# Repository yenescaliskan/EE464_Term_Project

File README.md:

# EE464_Term_Project
In this project, an isolated DC-DC converter (Push-Pull Converter) will be designed and implemented. Required converter will have 12-18V input voltage range and 48V output voltage. Output voltage will have at most 3% voltage ripple and output power rating will be 48W. Deviation of percent output voltage when input voltage is changed from its minimum to maximum will be at most 3%. Deviation of percent output voltage when load current is changed from 10% to 100% will be at most 3%.

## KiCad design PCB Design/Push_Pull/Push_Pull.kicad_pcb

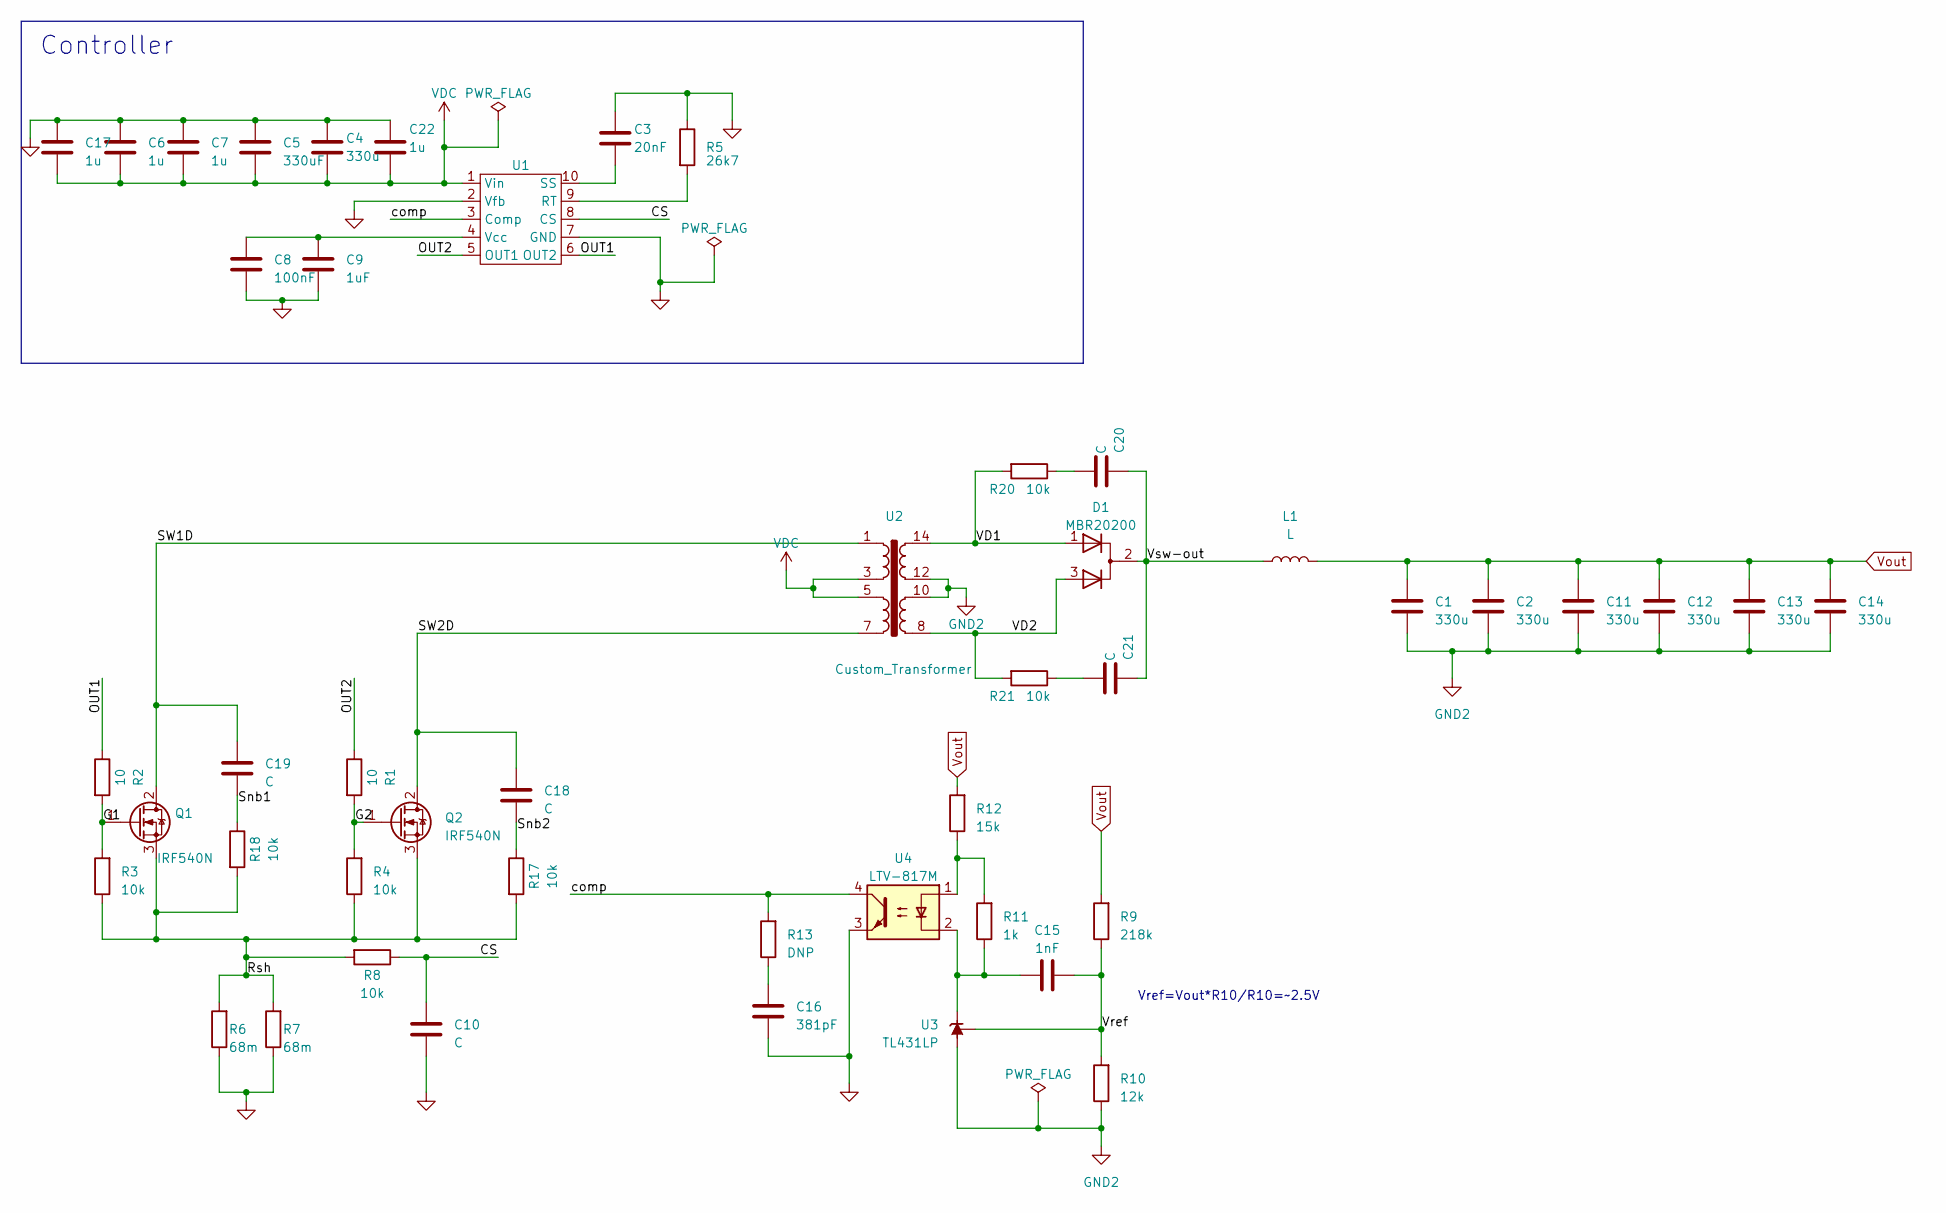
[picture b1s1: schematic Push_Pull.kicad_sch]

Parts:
C1, C2, C4, C11, C12, C13, C14: 330u; CP_Radial_D8.0mm_P5.00mm
C3: 20nF; C_Disc_D5.0mm_W2.5mm_P5.00mm
C5: 330uF; CP_Radial_D8.0mm_P5.00mm
C6, C7, C17, C22: 1u; C_0805_2012Metric
C8: 100nF; C_0603_1608Metric
C9: 1uF; C_0603_1608Metric
C10: C; C_Disc_D5.0mm_W2.5mm_P5.00mm
C15: 1nF; C_Disc_D5.1mm_W3.2mm_P5.00mm
C16: 381pF; C_Disc_D5.0mm_W2.5mm_P5.00mm
C18, C19: C; C_1206_3216Metric
C20, C21: C; C_Disc_D7.5mm_W5.0mm_P7.50mm
D1: MBR20200; TO-220-3_Vertical
L1: L; L_Toroid_Vertical_L25.4mm_W14.7mm_P12.20mm_Vishay_TJ5
Q1, Q2: IRF540N; TO-220-3_Vertical
R1, R2: 10; R_4020_10251Metric
R3, R4, R8: 10k; R_4020_10251Metric
R5: 26k7; R_Axial_DIN0204_L3.6mm_D1.6mm_P7.62mm_Horizontal
R6, R7: 68m; R_2512_6332Metric_Pad1.40x3.35mm_HandSolder
R9: 218k; R_Axial_DIN0207_L6.3mm_D2.5mm_P10.16mm_Horizontal
R10: 12k; R_Axial_DIN0207_L6.3mm_D2.5mm_P10.16mm_Horizontal
R11: 1k; R_Axial_DIN0207_L6.3mm_D2.5mm_P10.16mm_Horizontal
R12: 15k; R_Axial_DIN0207_L6.3mm_D2.5mm_P10.16mm_Horizontal
R13: DNP; R_Axial_DIN0204_L3.6mm_D1.6mm_P5.08mm_Horizontal
R17, R18: 10k; R_1206_3216Metric
R20, R21: 10k; R_Axial_DIN0207_L6.3mm_D2.5mm_P10.16mm_Horizontal
U1: DIP-10_W7.62mm
U2: Custom_Transformer; ETD34-14pin
U3: TL431LP; TO-92_Inline
U4: LTV-817M; DIP-4_W10.16mm

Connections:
/CS: C10.1, R8.1, U1.8 (CS)
/G1: Q1.1 (G), R2.2, R3.2
/G2: Q2.1 (G), R1.2, R4.2
/OUT1: R2.1, U1.6 (OUT2)
/OUT2: R1.1, U1.5 (OUT1)
/Rsh: Q1.3 (S), Q2.3 (S), R3.1, R4.1, R6.2, R7.2, R8.2, R17.2, R18.2
/SW1D: C19.1, Q1.2 (D), U2.1
/SW2D: C18.1, Q2.2 (D), U2.7
/Snb1: C19.2, R18.1
/Snb2: C18.2, R17.1
/VD1: D1.1 (K), R20.2, U2.14
/VD2: D1.3 (K), R21.2, U2.8
/Vref: C15.2, R9.1, R10.2, U3.1 (REF)
/Vsw-out: C20.1, C21.1, D1.2 (A), L1.1
/comp: R13.2, U1.3 (Comp), U4.4
GND: C3.1, C4.2, C5.2, C6.1, C7.1, C8.2, C9.2, C10.2, C16.1, C17.1, C22.1, R5.1, R6.1, R7.1, U1.2 (Vfb), U1.7 (GND), U4.3
GND2: C1.2, C2.2, C11.2, C12.2, C13.2, C14.2, R10.1, U2.10, U2.12, U3.2 (A)
unnamed: C16.2, R13.1
unnamed: C20.2, R20.1
unnamed: C21.2, R21.1
unnamed: R11.2, R12.1, U4.1
unnamed: R5.2, U1.9 (RT)
unnamed: C3.2, U1.10 (SS)
unnamed: C8.1, C9.1, U1.4 (Vcc)
unnamed: C15.1, R11.1, U3.3 (K), U4.2
VDC: C4.1, C5.1, C6.2, C7.2, C17.2, C22.2, U1.1 (Vin), U2.3, U2.5
Vout: C1.1, C2.1, C11.1, C12.1, C13.1, C14.1, L1.2, R9.2, R12.2

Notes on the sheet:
Controller
Vref=Vout*R10/R10=~2.5V

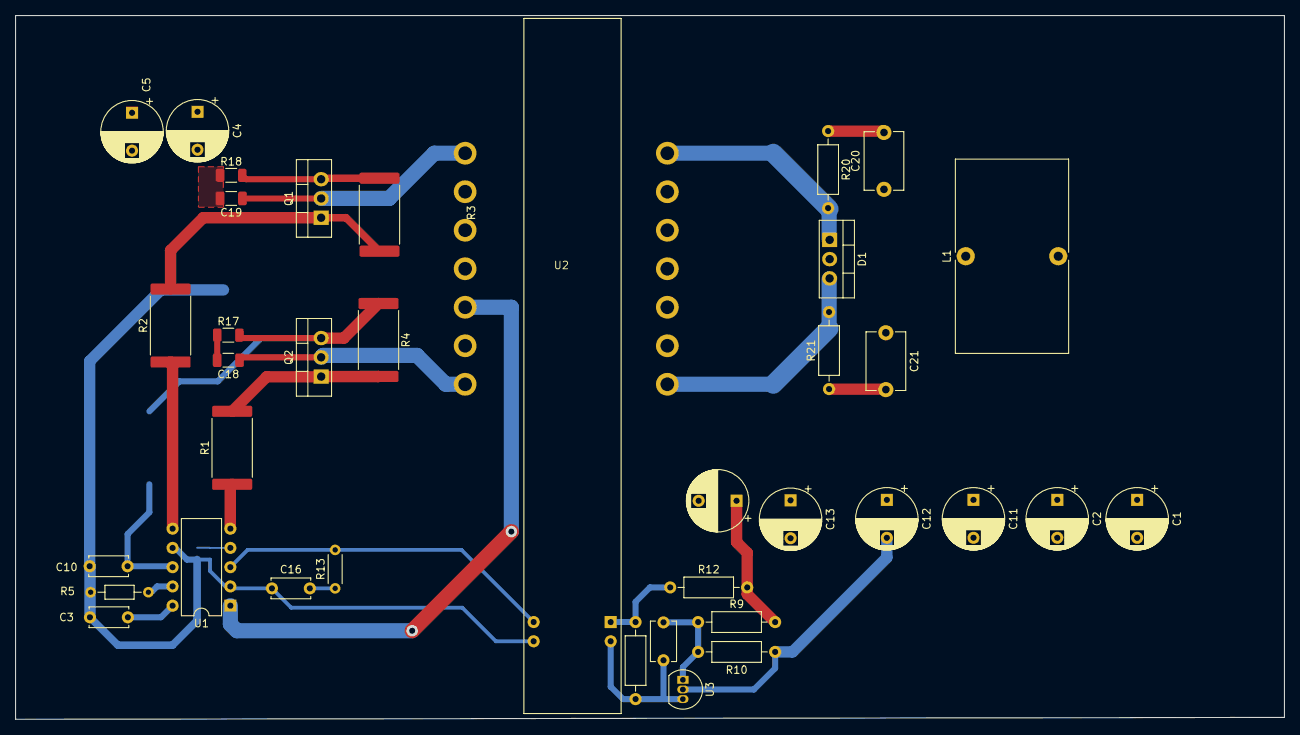
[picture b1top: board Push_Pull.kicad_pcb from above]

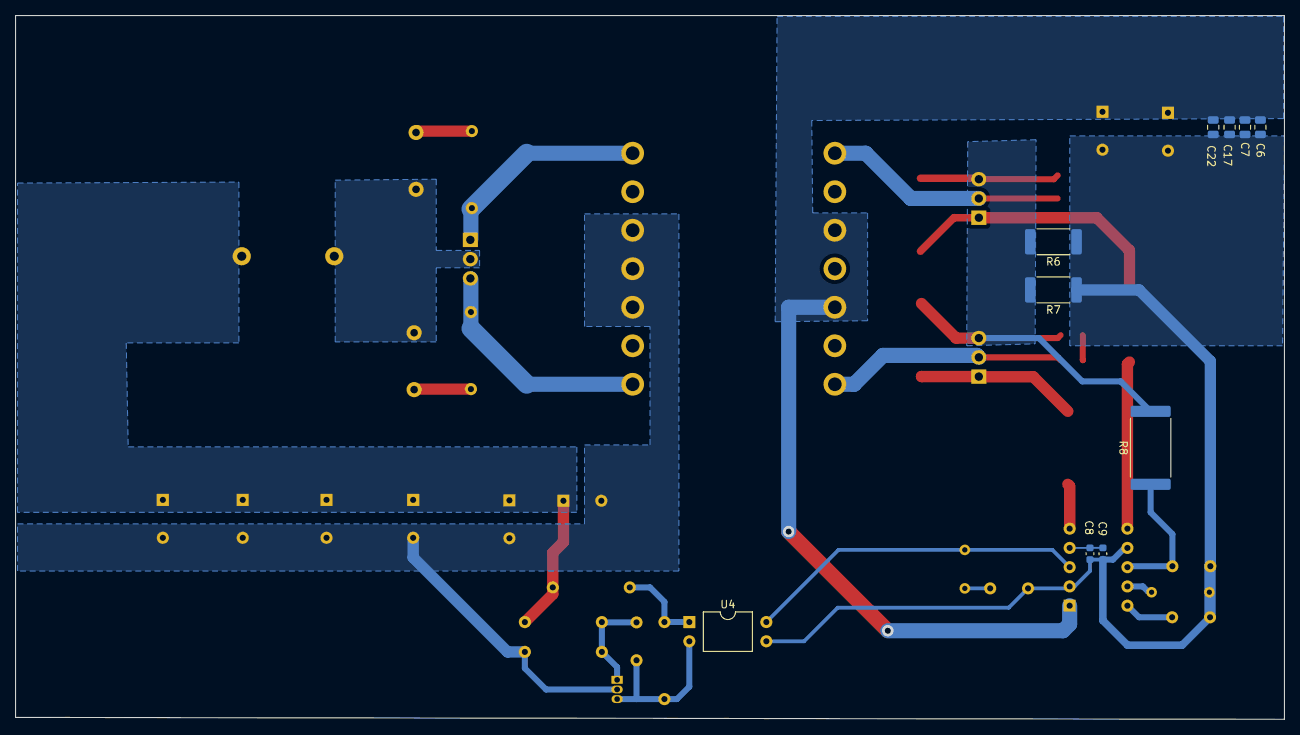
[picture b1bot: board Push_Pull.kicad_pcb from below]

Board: 2 copper layers, 167.4 x 92.8 mm, 47 parts (10 on the bottom side), 27 nets.

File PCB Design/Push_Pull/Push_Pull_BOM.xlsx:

Source: | C:\Users\smlmc\Documents\EE464_Term_Project\PCB Design\Push_Pull\Push_Pull.kica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
Date: | 45105.013958333337
Tool: | Eeschema 7.0.2
Generator: | C:\Program Files\KiCad\7.0\bin\scripting\plugins/bom_csv_grouped_by_value.py
Component Count: | 47
Collated Components:
Item | Qty | Reference(s) | Value | LibPart | Footprint | Datasheet | DNP
1 | 7 | C1, C2, C4, C11, C12, C13, C14 | 330u | Device:C | Capacitor_THT:CP_Radial_D8.0mm_P5.00mm | ~
2 | 1 | C3 | 20nF | Device:C | Capacitor_THT:C_Disc_D5.0mm_W2.5mm_P5.00mm | ~
3 | 1 | C5 | 330uF | Device:C | Capacitor_THT:CP_Radial_D8.0mm_P5.00mm | ~
4 | 4 | C6, C7, C17, C22 | 1u | Device:C | Capacitor_SMD:C_0805_2012Metric | ~
5 | 1 | C8 | 100nF | Device:C | Capacitor_SMD:C_0603_1608Metric | ~
6 | 1 | C9 | 1uF | Device:C | Capacitor_SMD:C_0603_1608Metric | ~
7 | 1 | C10 | C | Device:C | Capacitor_THT:C_Disc_D5.0mm_W2.5mm_P5.00mm | ~
8 | 1 | C15 | 1nF | Device:C | Capacitor_THT:C_Disc_D5.1mm_W3.2mm_P5.00mm | ~
9 | 1 | C16 | 381pF | Device:C | Capacitor_THT:C_Disc_D5.0mm_W2.5mm_P5.00mm | ~
10 | 2 | C18, C19 | C | Device:C | Capacitor_SMD:C_1206_3216Metric | ~
11 | 2 | C20, C21 | C | Device:C | Capacitor_THT:C_Disc_D7.5mm_W5.0mm_P7.50mm | ~
12 | 1 | D1 | MBR20200 | Device:D_Dual_CommonCathode_AKA_Parallel | Package_TO_SOT_THT:TO-220-3_Vertical | ~
13 | 1 | L1 | L | Device:L | Inductor_THT:L_Toroid_Vertical_L25.4mm_W14.7mm_P12.20mm_Vishay_TJ5 | ~
14 | 2 | Q1, Q2 | IRF540N | Transistor_FET:IRF540N | Package_TO_SOT_THT:TO-220-3_Vertical | http://www.irf.com/product-info/datasheets/data/irf540n.pdf
15 | 2 | R1, R2 | 10 | Device:R | Resistor_SMD:R_4020_10251Metric | ~
16 | 3 | R3, R4, R8 | 10k | Device:R | Resistor_SMD:R_4020_10251Metric | ~
17 | 1 | R5 | 26k7 | Device:R | Resistor_THT:R_Axial_DIN0204_L3.6mm_D1.6mm_P7.62mm_Horizontal | ~
18 | 2 | R6, R7 | 68m | Device:R | Resistor_SMD:R_2512_6332Metric_Pad1.40x3.35mm_HandSolder | ~
19 | 1 | R9 | 218k | Device:R | Resistor_THT:R_Axial_DIN0207_L6.3mm_D2.5mm_P10.16mm_Horizontal | ~
20 | 1 | R10 | 12k | Device:R | Resistor_THT:R_Axial_DIN0207_L6.3mm_D2.5mm_P10.16mm_Horizontal | ~
21 | 1 | R11 | 1k | Device:R | Resistor_THT:R_Axial_DIN0207_L6.3mm_D2.5mm_P10.16mm_Horizontal | ~
22 | 1 | R12 | 15k | Device:R | Resistor_THT:R_Axial_DIN0207_L6.3mm_D2.5mm_P10.16mm_Horizontal | ~
23 | 1 | R13 | DNP | Device:R | Resistor_THT:R_Axial_DIN0204_L3.6mm_D1.6mm_P5.08mm_Horizontal | ~
24 | 2 | R17, R18 | 10k | Device:R | Resistor_SMD:R_1206_3216Metric | ~
25 | 2 | R20, R21 | 10k | Device:R | Resistor_THT:R_Axial_DIN0207_L6.3mm_D2.5mm_P10.16mm_Horizontal | ~
26 | 1 | U1 | ~ | EE464-Symbols:LM5030-DIP | Package_DIP:DIP-10_W7.62mm
27 | 1 | U2 | Custom_Transformer | EE464-Symbols:Custom_Transformer | Push-Pull:ETD34-14pin
28 | 1 | U3 | TL431LP | Reference_Voltage:TL431LP | Package_TO_SOT_THT:TO-92_Inline | http://www.ti.com/lit/ds/symlink/tl431.pdf
29 | 1 | U4 | LTV-817M | Isolator:LTV-817M | Package_DIP:DIP-4_W10.16mm | http://www.us.liteon.com/downloads/LTV-817-827-847.PDF

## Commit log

2023-05-16 Push-Pull Controller is added, feedback design app note added
2023-06-27 All related files were added to project repository.
2023-06-27 PCB Design files are added
2023-06-27 Used components, cost and BOM is added
2023-06-28 Simulation and test results parts of final report were written.
2023-06-28 thermal camera image was added.
2023-06-28 Thermal Calculations
2023-06-28 Report is completed final report pdf is added
